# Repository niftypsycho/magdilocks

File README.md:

# magdilocks
 Hall effect sensor carrier board
  
This project uses the master-vampire library located in niftypsycho/master-vampire.  
  
In order to modifiy the project you will need to clone the master-vampire repository into the same directory that encompasses where magdilocks is cloned.  
  
Example:  
```
|GitHub  
    |magdilocks  
    |master-vampire
```
The library components are setup in the project to point to a relative path to master-vampire in this configuration.

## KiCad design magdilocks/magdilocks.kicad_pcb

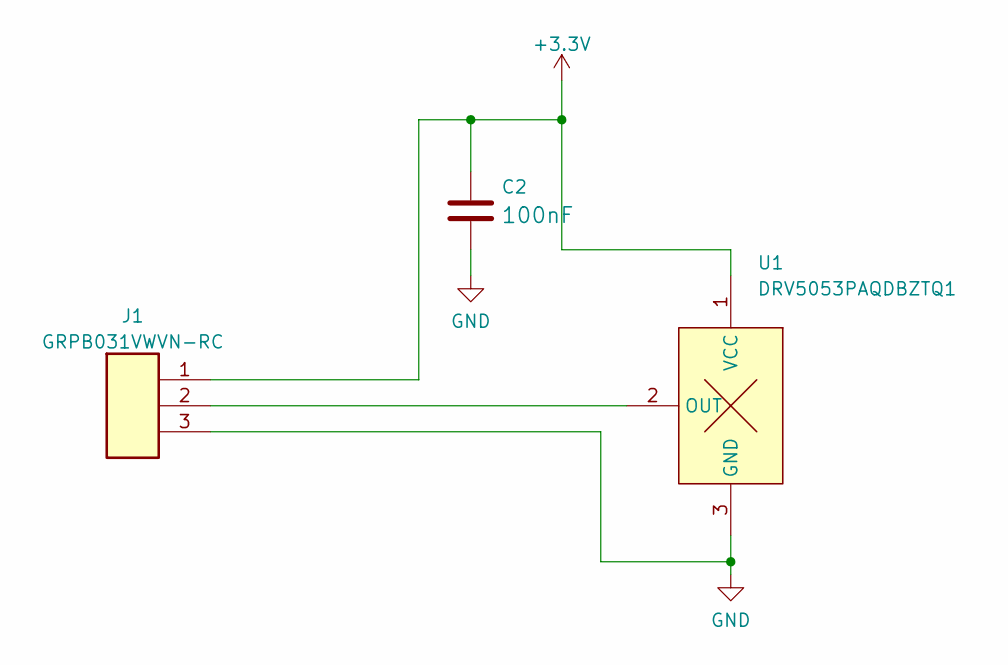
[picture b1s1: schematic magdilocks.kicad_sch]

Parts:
C2: C; C_0805; Voltage Rating 50V; Tolerance 20per; MPN CL21B104KACNNNC; LCSC C695378
J1: Conn_1x3; CONN_HEADER_MALE_1X3PIN_P1.27MM_TH_Phob; MPN GRPB031VWVN-RC
U1: U_DRV5053; SOT-23-3; MPN DRV5053PAQDBZTQ1

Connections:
+3V3: C2.1, J1.1, U1.1 (VCC)
GND: C2.2, J1.3, U1.3 (GND)
unnamed: J1.2, U1.2 (OUT)

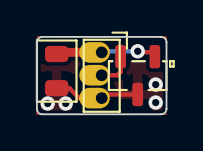
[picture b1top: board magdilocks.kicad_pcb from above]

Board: 2 copper layers, 7.2 x 4.3 mm, 3 parts (0 on the bottom side), 3 nets.

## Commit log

2022-06-26 First commit
    Created project, basically finished preliminary design.
2022-07-03 Initial design
    Commit of v1.0 design and fabrication files
2022-07-04 v2.0 Release
    Modified board shape to fit on Phob 1.2.2. Changed pin assignments for development headers.
2022-07-05 V2.0 production release
    Fixed board shape to fit main board and c-stick PBCs. Created gerber/drill files, BOM export, 3D model, and render examples on Phob 1.2.2.
2022-07-05 Moved BOM
    Put BOM in production directory
